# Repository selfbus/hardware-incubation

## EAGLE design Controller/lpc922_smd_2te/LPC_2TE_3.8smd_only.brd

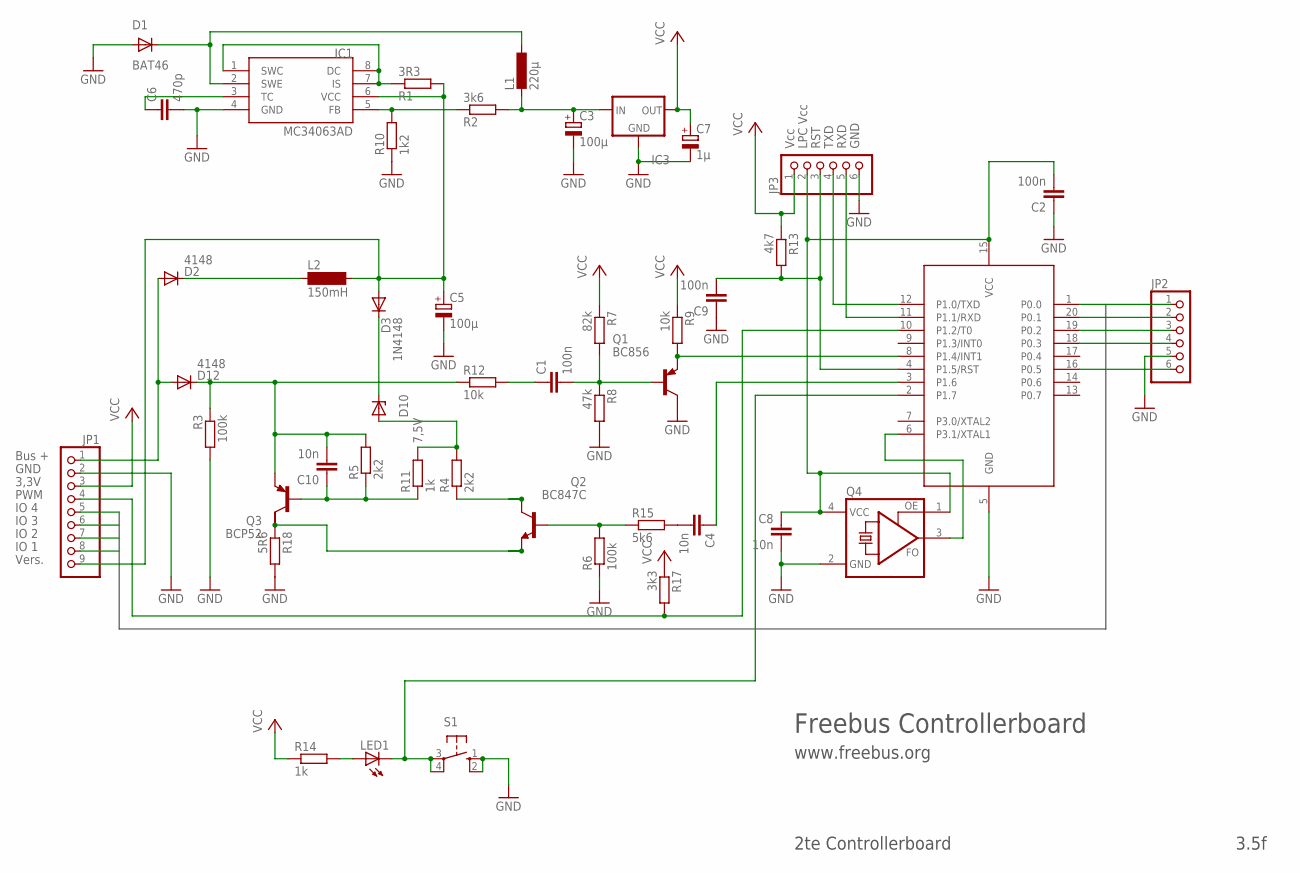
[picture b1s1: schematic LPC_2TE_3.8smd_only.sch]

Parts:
C1, C2, C9: 100n; C1206
C3: 100µ; E2,5-6
C4, C8, C10: 10n; C1206
C5: 100µ; E3,5-8
C6: 470p; C1206
C7: 1µ; E2-5
D1: BAT46; MINIMELF
D2, D12: 4148; MINIMELF
D3: 1N4148; MINIMELF
D10: 7,5V; MINIMELF
IC1: MC34063AD; SOIC8
IC2: LPC922FDH; TSSOP20
IC3: 79LXX
JP1: PINHD-1X9; 1X09
JP2, JP3: PINHD-1X6; 1X06
L1: 220µ; 0207/12
L2: 150mH; BS11
LED1: LED3MM
Q1: BC856; SOT23-BEC
Q2: BC847C; SOT23
Q3: BCP52; SOT223
Q4: ASFL1; ASF
R1: 3R3; R1206
R2: 3k6; R1206
R3, R6: 100k; R1206
R4, R5: 2k2; R1206
R7: 82k; R1206
R8: 47k; R1206
R9, R12: 10k; R1206
R10: 1k2; R1206
R11, R14: 1k; R1206
R13: 4k7; R1206
R15: 5k6; R1206
R17: 3k3; R1206
R18: 5R6; R1206
S1: 10-XX; B3F-10XX

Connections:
/RESET: C9.2, IC2.4 (P1.5/RST), JP3.3, R13.2
BASE: C1.2, Q1.B, R7.2, R8.1
BASE_SEND: Q2.1 (B), R6.2, R15.1
EIB+: D2.A, D12.A, JP1.1
EIB_DC: C5.+, D3.A, IC1.6 (VCC), JP1.9, L2.2, R1.2
FEEDBACK: IC1.5 (FB), R2.1, R10.2
GND: C2.1, C3.-, C5.-, C6.2, C7.-, C8.2, C9.1, D1.A, IC1.4 (GND), IC2.5 (GND), IC3.GND, JP1.2, JP2.5, JP3.6, Q1.C, Q4.2 (GND), R3.2, R6.1, R8.2, R10.1, R18.2, S1.1 (S), S1.2 (S1)
I_SENSE: Q2.2 (E), Q3.2 (C), R18.1
unnamed: Q2.3 (C), R4.1
unnamed: C10.2, D12.C, Q3.3 (E), R3.1, R5.2, R12.1
unnamed: IC2.6 (P3.1/XTAL1), Q4.3 (FO)
unnamed: IC1.1 (SWC), IC1.7 (IS), IC1.8 (DC), R1.1
unnamed: LED1.A, R14.2
unnamed: D2.C, L2.1
unnamed: C6.1, IC1.3 (TC)
unnamed: D3.C, D10.C
unnamed: C1.1, R12.2
unnamed: C4.2, R15.2
unnamed: C10.1, Q3.1 (B), R5.1, R11.1
P0.0: IC2.1 (P0.0), JP1.8, JP2.1
P0.1: IC2.20 (P0.1), JP1.7, JP2.2
P0.2: IC2.19 (P0.2), JP1.6, JP2.3
P0.3: IC2.18 (P0.3), JP1.5, JP2.4
P0.5: IC2.16 (P0.5), JP2.6
PROG: IC2.2 (P1.7), LED1.K (C), S1.3, S1.4 (P1)
PWM: IC2.10 (P1.2/T0), JP1.4, R17.2
REFERENZ: D10.A, R4.2, R11.2
RXD: IC2.11 (P1.1/RXD), JP3.5
SIGIN: IC2.8 (P1.4/INT1), Q1.E, R9.2
SIGOUT: C4.1, IC2.3 (P1.6)
SWITCHED: D1.C, IC1.2 (SWE), L1.1
TXD: IC2.12 (P1.0/TXD), JP3.4
VCC: C7.+, IC3.OUT, JP1.3, JP3.1, R7.1, R9.1, R13.1, R14.1, R17.1
VCC_5V: C3.+, IC3.IN, L1.2, R2.2
VCC_LPC: C2.2, C8.1, IC2.15 (VCC), JP3.2, Q4.1 (OE), Q4.4 (VCC)

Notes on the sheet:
Bus +
GND
3,3V
PWM
IO 1
IO 2
IO 3
IO 4
Vcc
LPC Vcc
RST
TXD
RXD
Vers.
Freebus Controllerboard
www.freebus.org
2te Controllerboard
3.5f

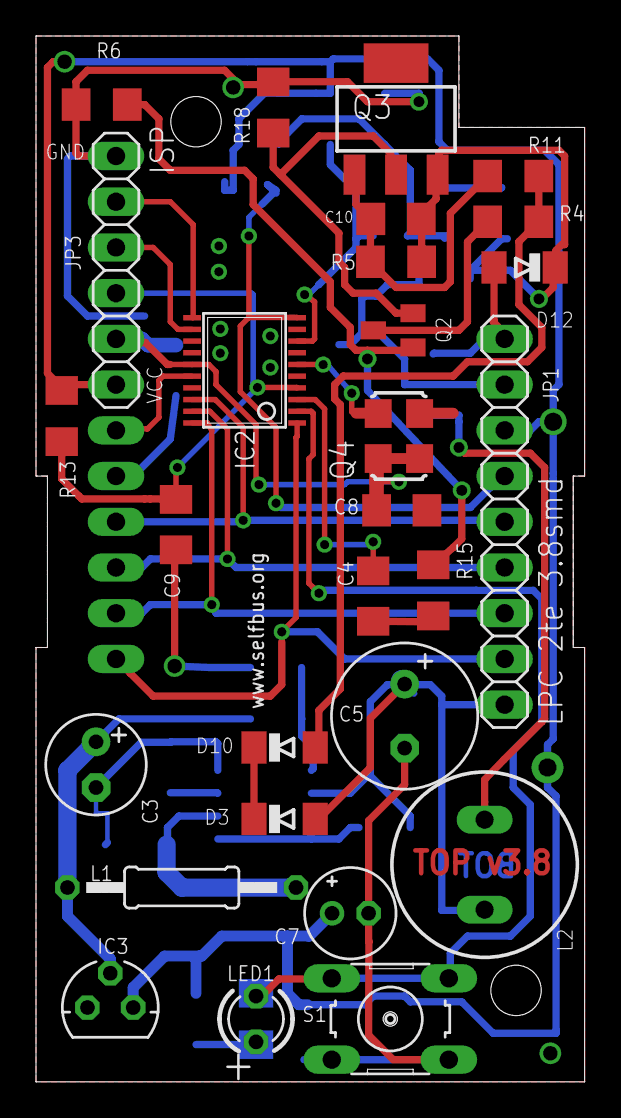
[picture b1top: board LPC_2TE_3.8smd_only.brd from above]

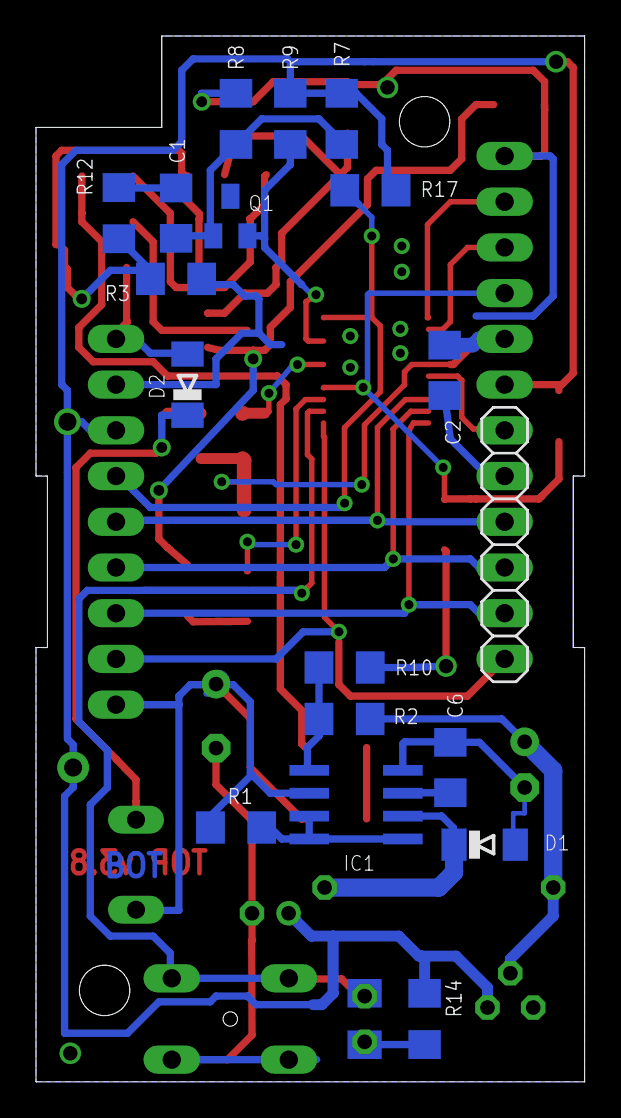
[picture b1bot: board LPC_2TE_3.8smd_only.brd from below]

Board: 2 copper layers, 30.5 x 58.1 mm, 46 parts (18 on the bottom side), 35 nets.
